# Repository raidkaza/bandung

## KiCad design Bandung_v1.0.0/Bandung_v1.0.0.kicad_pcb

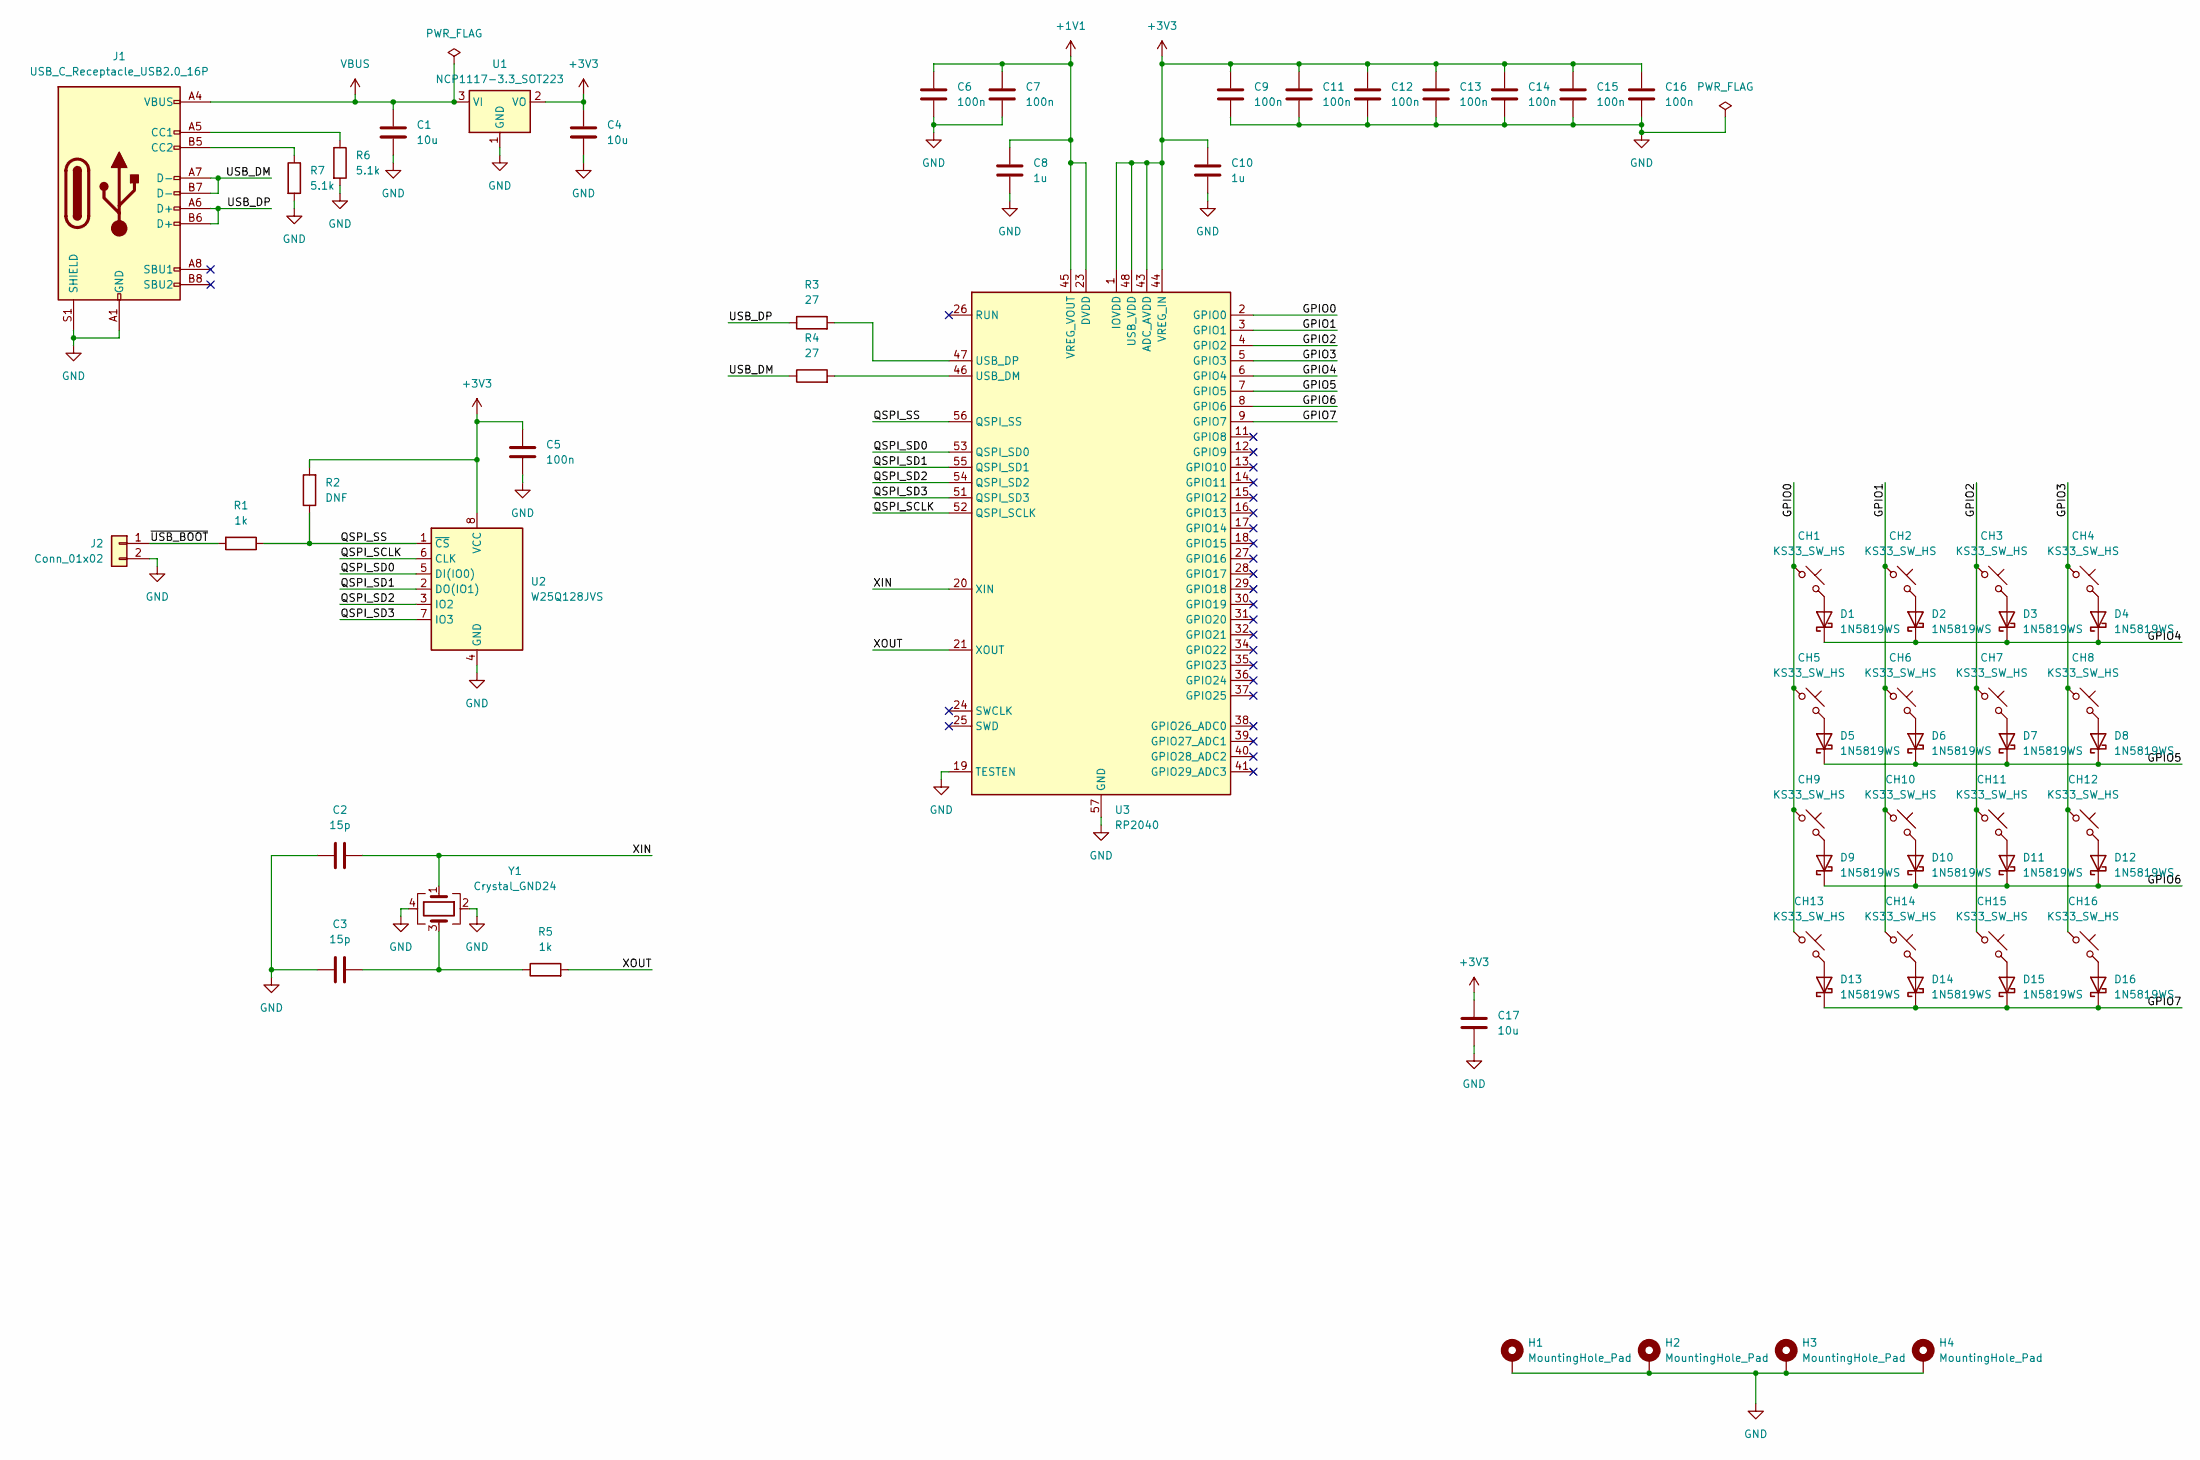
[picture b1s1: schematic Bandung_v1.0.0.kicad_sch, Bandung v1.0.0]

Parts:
C1, C4, C17: 10u; C_0805_2012Metric
C2, C3: 15p; C_0402_1005Metric
C5, C6, C7, C9, C11, C12, C13, C14, C15, C16: 100n; C_0402_1005Metric
C8, C10: 1u; C_0402_1005Metric
CH1, CH2, CH3, CH4, CH5, CH6, CH7, CH8, CH9, CH10, CH11, CH12, CH13, CH14, CH15, CH16: KS33_SW_HS; SW_KS33_HS_KS-2P02B01-02_HS_1u
D1, D2, D3, D4, D5, D6, D7, D8, D9, D10, D11, D12, D13, D14, D15, D16: 1N5819WS; D_SOD-323
H1, H2, H3, H4: MountingHole_Pad; MountingHole_3.2mm_M3_Pad_Via
J1: USB_C_Receptacle_USB2.0_16P; USB_C_Receptacle_GCT_USB4085
J2: Conn_01x02; PinHeader_1x02_P2.54mm_Vertical
R1, R5: 1k; R_0402_1005Metric
R2: DNF; R_0402_1005Metric
R3, R4: 27; R_0402_1005Metric
R6, R7: 5.1k; R_0402_1005Metric
U1: NCP1117-3.3_SOT223; SOT-223-3_TabPin2
U2: W25Q128JVS; SOIC-8_5.23x5.23mm_P1.27mm
U3: RP2040; QFN-56-1EP_7x7mm_P0.4mm_EP3.2x3.2mm
Y1: Crystal_GND24; Crystal_SMD_3225-4Pin_3.2x2.5mm

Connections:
+1V1: C6.1, C7.1, C8.1, U3.23 (DVDD), U3.45 (VREG_VOUT), U3.50 (DVDD)
+3V3: C4.1, C5.1, C9.1, C10.1, C11.1, C12.1, C13.1, C14.1, C15.1, C16.1, C17.1, R2.2, U1.2 (VO), U2.8 (VCC), U3.1 (IOVDD), U3.10 (IOVDD), U3.22 (IOVDD), U3.33 (IOVDD), U3.42 (IOVDD), U3.43 (ADC_AVDD), U3.44 (VREG_IN), U3.48 (USB_VDD), U3.49 (IOVDD)
/GPIO0: CH1.1, CH5.1, CH9.1, CH13.1, U3.2 (GPIO0)
/GPIO1: CH2.1, CH6.1, CH10.1, CH14.1, U3.3 (GPIO1)
/GPIO2: CH3.1, CH7.1, CH11.1, CH15.1, U3.4 (GPIO2)
/GPIO3: CH4.1, CH8.1, CH12.1, CH16.1, U3.5 (GPIO3)
/GPIO4: D1.1 (K), D2.1 (K), D3.1 (K), D4.1 (K), U3.6 (GPIO4)
/GPIO5: D5.1 (K), D6.1 (K), D7.1 (K), D8.1 (K), U3.7 (GPIO5)
/GPIO6: D9.1 (K), D10.1 (K), D11.1 (K), D12.1 (K), U3.8 (GPIO6)
/GPIO7: D13.1 (K), D14.1 (K), D15.1 (K), D16.1 (K), U3.9 (GPIO7)
/QSPI_SCLK: U2.6 (CLK), U3.52 (QSPI_SCLK)
/QSPI_SD0: U2.5 (DI(IO0)), U3.53 (QSPI_SD0)
/QSPI_SD1: U2.2 (DO(IO1)), U3.55 (QSPI_SD1)
/QSPI_SD2: U2.3 (IO2), U3.54 (QSPI_SD2)
/QSPI_SD3: U2.7 (IO3), U3.51 (QSPI_SD3)
/QSPI_SS: R1.1, R2.1, U2.1 (~CS), U3.56 (QSPI_SS)
/USB_DM: J1.A7 (D-), J1.B7 (D-), R4.1
/USB_DP: J1.A6 (D+), J1.B6 (D+), R3.1
/XIN: C2.2, U3.20 (XIN), Y1.1
/XOUT: R5.2, U3.21 (XOUT)
/~USB_BOOT: J2.1, R1.2
GND: C1.2, C2.1, C3.1, C4.2, C5.2, C6.2, C7.2, C8.2, C9.2, C10.2, C11.2, C12.2, C13.2, C14.2, C15.2, C16.2, C17.2, H1.1, H2.1, H3.1, H4.1, J1.A1 (GND), J1.A12 (GND), J1.B1 (GND), J1.B12 (GND), J1.S1 (SHIELD), J2.2, R6.2, R7.2, U1.1 (GND), U2.4 (GND), U3.19 (TESTEN), U3.57 (GND), Y1.2, Y1.4
unnamed: C3.2, R5.1, Y1.3
unnamed: CH1.2, D1.2 (A)
unnamed: CH2.2, D2.2 (A)
unnamed: CH3.2, D3.2 (A)
unnamed: CH4.2, D4.2 (A)
unnamed: CH5.2, D5.2 (A)
unnamed: CH6.2, D6.2 (A)
unnamed: CH7.2, D7.2 (A)
unnamed: CH8.2, D8.2 (A)
unnamed: CH9.2, D9.2 (A)
unnamed: CH10.2, D10.2 (A)
unnamed: CH11.2, D11.2 (A)
unnamed: CH12.2, D12.2 (A)
unnamed: CH13.2, D13.2 (A)
unnamed: CH14.2, D14.2 (A)
unnamed: CH15.2, D15.2 (A)
unnamed: CH16.2, D16.2 (A)
unnamed: J1.A5 (CC1), R6.1
unnamed: J1.B5 (CC2), R7.1
unnamed: R4.2, U3.46 (USB_DM)
unnamed: R3.2, U3.47 (USB_DP)
VBUS: C1.1, J1.A4 (VBUS), J1.A9 (VBUS), J1.B4 (VBUS), J1.B9 (VBUS), U1.3 (VI)

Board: 2 copper layers, 66 parts (62 on the bottom side), 44 nets, no tracks yet.
